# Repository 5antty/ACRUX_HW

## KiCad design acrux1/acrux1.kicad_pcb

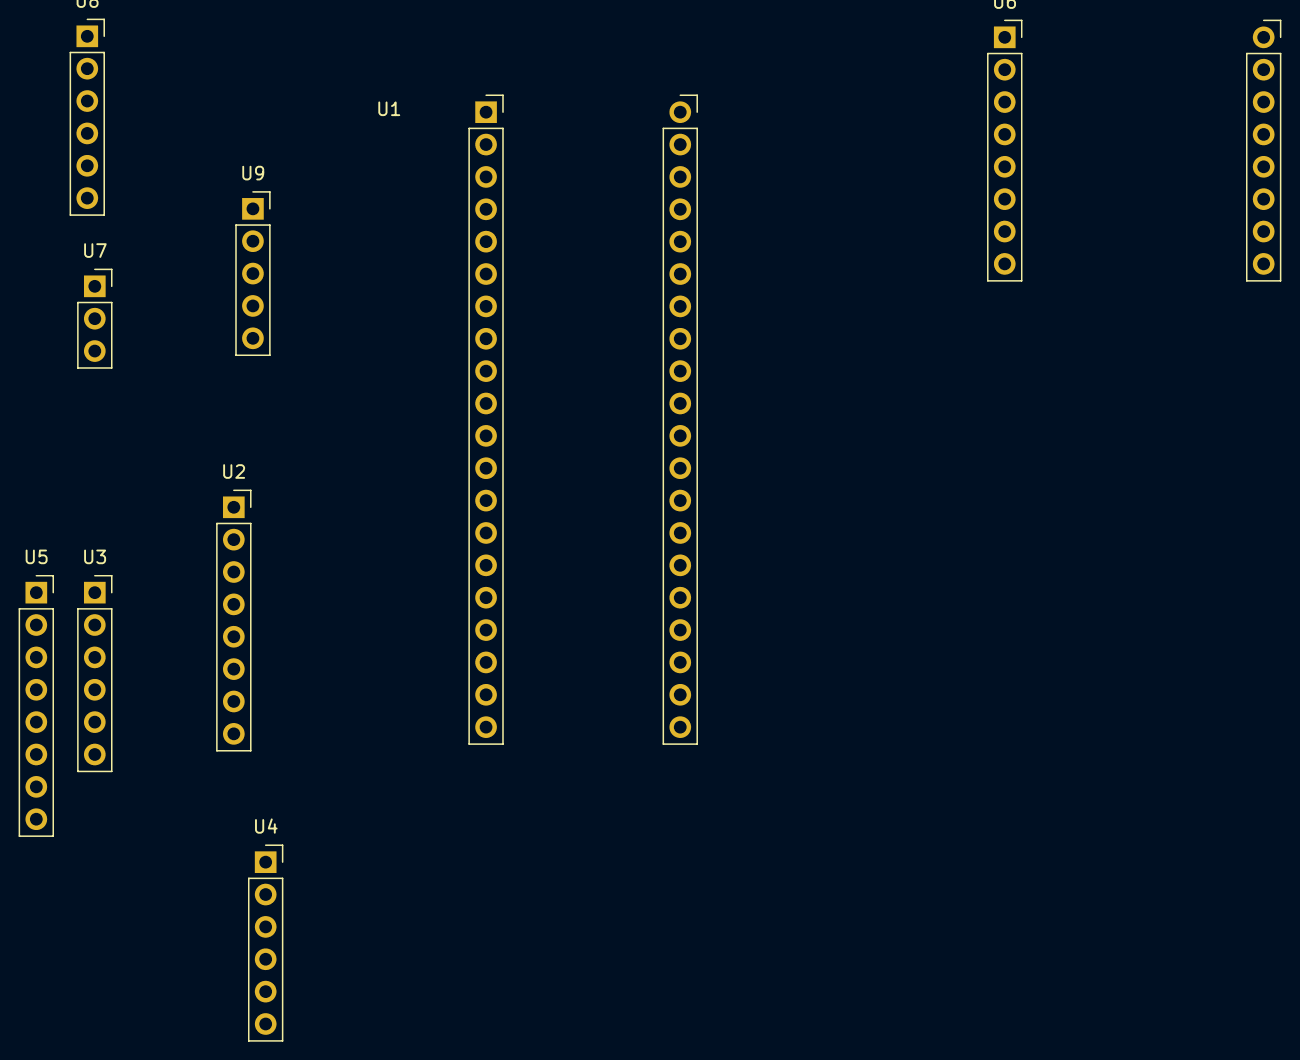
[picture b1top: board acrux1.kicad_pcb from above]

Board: 2 copper layers, 9 parts (0 on the bottom side), 17 nets, no tracks yet.

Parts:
U1: BluePill_Connector; tira de pines
U2, U5: BMP390; tira de pines hembra
U3, U4: LSM6DSOX; tira de pines
U6: SX1278; tira de pines
U7: BuzzerActivo; tira de pinnes
U8: Modulo mem flash; tira de pinnes modulo
U9: Encoder; tira de pinnes

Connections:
+3.3V: U1.20 (3.3), U2.1 (VIN), U3.1 (VIN), U4.1 (VIN), U5.1 (VIN), U6.3 (3.3), U7.2 (VCC), U8.1 (VCC), U9.2 (VCC)
/GPIO_Buzzer: U1.5 (A8), U7.3 (Signal)
/I2C1_SCL: U1.14 (B6), U2.4 (SCL), U3.4 (SCL), U4.4 (SCL), U4.5 (SDA), U5.4 (SCL)
/I2C1_SDA: U1.15 (B7), U2.6 (SDA), U3.5 (SDA), U5.6 (SDA)
/LoRa_DIO0: U1.27 (B1), U6.5 (DIO0)
/LoRa_RST: U1.28 (B0), U6.4 (RST)
/SPI1_MISO: U1.30 (A6), U6.12 (MISO)
/SPI1_MOSI: U1.29 (A7), U6.11 (MOSI)
/SPI1_SCK: U1.31 (A5), U6.13 (SCK)
/SPI1_SS: U1.32 (A4), U6.10 (NSS)
/SPI2_MISO: U1.3 (B14), U8.3 (DO)
/SPI2_MOSI: U1.4 (B15), U8.6 (DI)
/SPI2_SCK: U1.2 (B13), U8.5 (CLK)
/SPI2_SS: U1.1 (B12), U8.2 (CS)
/TIM2CH1_Encoder: U1.10 (A15), U9.5 (CLK)
/TIM2CH2_Encoder: U1.11 (B3), U9.4 (DT)
GND: U1.19 (GND), U2.3 (GND), U3.3 (GND), U4.3 (GND), U5.3 (GND), U6.16 (GND), U7.1 (GND), U8.4 (GND), U9.1 (GND)
